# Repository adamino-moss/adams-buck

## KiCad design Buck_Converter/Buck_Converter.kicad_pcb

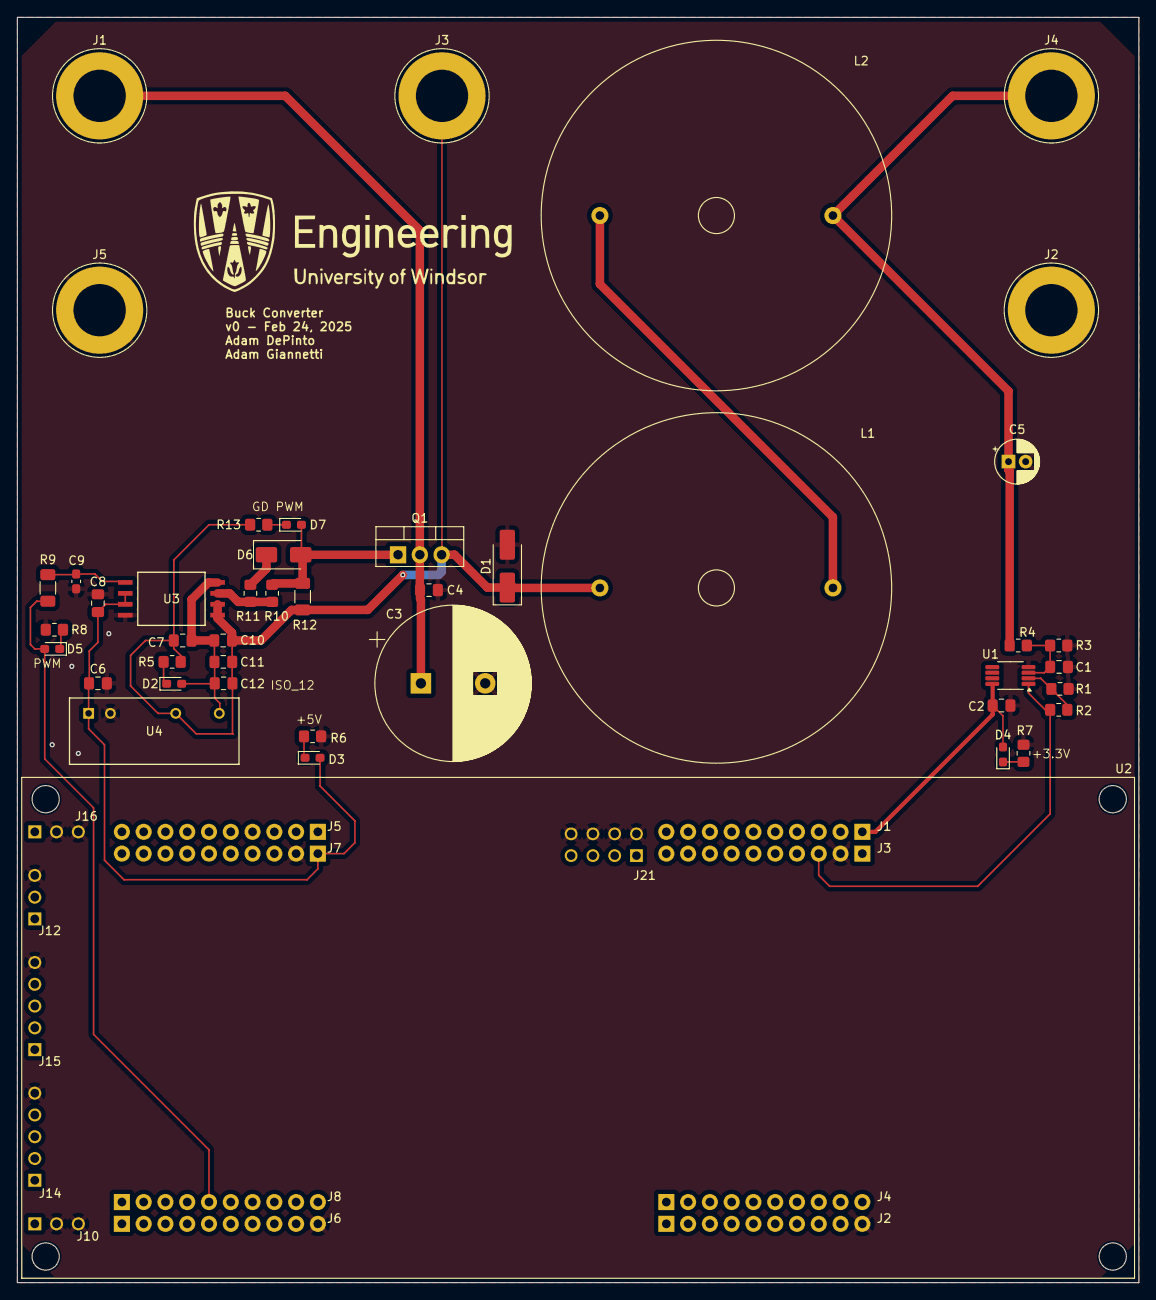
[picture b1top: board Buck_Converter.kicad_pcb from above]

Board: 2 copper layers, 130.8 x 147.6 mm, 44 parts (0 on the bottom side), 21 nets.

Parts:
C1: 1.2u; C_0805_2012Metric_Pad1.18x1.45mm_HandSolder
C2, C4, C6, C7, C8: 1u; C_0805_2012Metric_Pad1.18x1.45mm_HandSolder
C3: 470u; CP_Radial_D18.0mm_P7.50mm
C5: 3.3u; CP_Radial_D5.0mm_P2.00mm
C9: 33pF; C_0603_1608Metric_Pad1.08x0.95mm_HandSolder
C10, C12: 10u; C_0805_2012Metric_Pad1.18x1.45mm_HandSolder
C11: 220n; C_0805_2012Metric_Pad1.18x1.45mm_HandSolder
D1: SS310; D_SMA_Handsoldering
D2, D3, D4, D5, D7: LTST-C190GKT; LED_0603_1608Metric_Pad1.05x0.95mm_HandSolder
D6: US2AA; D_SMA
J1, J2, J3, J4, J5: Conn_01x01_Pin; Banana_Jack_1Pin
L1, L2: 12m; L_Radial_D40.6mm_P27.18mm_Vishay_IHB-4
Q1: IRF540N; TO-220-3_Vertical
R1, R4: 40k; R_0805_2012Metric_Pad1.20x1.40mm_HandSolder
R2, R3: 2k; R_0805_2012Metric_Pad1.20x1.40mm_HandSolder
R5, R13: 1k; R_0805_2012Metric_Pad1.20x1.40mm_HandSolder
R6: 300; R_0805_2012Metric_Pad1.20x1.40mm_HandSolder
R7, R8: 120; R_0805_2012Metric_Pad1.20x1.40mm_HandSolder
R9: 51; R_1206_3216Metric_Pad1.30x1.75mm_HandSolder
R10: 7.5; R_0805_2012Metric_Pad1.20x1.40mm_HandSolder
R11: 12; R_0805_2012Metric_Pad1.20x1.40mm_HandSolder
R12: 50; R_1206_3216Metric_Pad1.30x1.75mm_HandSolder
U1: LM358; VSSOP-8_3x3mm_P0.65mm
U2: LAUNCHXL-F28379D; MOD_LAUNCHXL-F28379D
U3: UCC5304DWVR; SOIC8_DWV_TEX
U4: TMV 0512SHI; TMV-HI_SINGLE_TRP

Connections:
+3.3V: C2.1, D4.2 (A), U1.8 (V+), U2.J1_1 (3.3V_J1)
+5V: C6.1, C8.1, D3.2 (A), U2.J7_1 (+5V_J7), U3.2 (VCCI), U3.3 (VCCI), U4.1 (+VIN(VCC))
/GD/GD_PWM: R10.1, R11.1, U3.7 (OUT)
/GD/ISO_12: C7.1, C10.1, C11.1, C12.1, D2.2 (A), U3.8 (VDD), U4.7 (+VOUT)
/GD/PWM_FILT: C9.1, R9.2, U3.1 (IN)
/PWM: D5.2 (A), R9.1, U2.J8_5 (GPIO11/PWMOUT6B)
/PowerStage/VIN: C3.1, C4.1, J1.1, Q1.2 (D)
/VFILT: R2.2, U1.1, U2.J3_3 (ADCIN14/ANALOGIN)
/VG: D6.2 (A), D7.2 (A), Q1.1 (G), R10.2, R12.2
/VOUT: C5.1, J4.1, L2.2, R4.2
/VSW: C7.2, C10.2, C11.2, C12.2, D1.1 (K), J3.1, L1.1, Q1.3 (S), R5.2, R12.1, R13.2, U3.5 (VSS), U3.6 (VSS), U4.5 (-VOUT)
GND: C1.2, C2.2, C3.2, C4.2, C5.2, C6.2, C8.2, C9.2, D1.2 (A), J2.1, J5.1, R1.1, R3.1, R6.2, R7.2, R8.2, U1.4 (V-), U2.J2_10 (GND_J2), U2.J3_2 (GND_J3), U2.J6_10 (GND_J6), U2.J7_2 (GND_J7), U2.J10_2 (GND_J10), U2.J10_3 (GND_J10__1), U2.J12_3 (GND_J12), U2.J14_5 (GND_J14), U2.J15_5 (GND_J15), U2.J16_2 (GND_J16), U2.J16_3 (GND_J16__1), U2.J21_2 (TP21/GND), U2.J21_4 (TP22/GND), U2.J21_6 (TP23/GND), U2.J21_8 (TP24/GND), U3.4 (GND), U4.2 (-VIN(GGND))
unnamed: D2.1 (K), R5.1
unnamed: D3.1 (K), R6.1
unnamed: D4.1 (K), R7.1
unnamed: D5.1 (K), R8.1
unnamed: D6.1 (K), R11.2
unnamed: D7.1 (K), R13.1
unnamed: L1.2, L2.1
unnamed: C1.1, R3.2, R4.1, U1.3 (+)
unnamed: R1.2, R2.1, U1.2 (-)

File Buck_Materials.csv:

Reference,Value,Qty,DNP,#,Part Number
D6,US2AA,1,,1,US2AA
U3,UCC5304DWVR,1,,2,UCC5304DWVR
U4,TMV 0512SHI,1,,3,TMV 0512SHI
"C2,C6,C7,C8",1u,4,,4,TAJR105K025RNJ
D1,SS310,1,,5,SS310
"R5,R13",1k,2,,6,RNCP0805FTD1K00
R6,300,1,,7,RMCF0805JT300R
"R7,R8",120,2,,8,RMCF0805FT120R
R12,50,1,,9,RCP1206W50R0JTP
R9,51,1,,10,RC1206FR-0751RL
R11,12,1,,11,RC0805FR-0712RL
"R2,R3",2k,2,,12,RC0805FR-072KL
"D2,D3,D4,D5,D7",LTST-C190GKT,5,,13,LTST-C190GKT
U1,LM358,1,,14,LM358DGKR
U2,LAUNCHXL-F28379D,1,,15,LAUNCHXL-F28379D
Q1,IRF540N,1,,16,IRF540NPBF
C12,10u,1,,17,GRM21BR61E106KA73L
C4,1u,1,,18,GRM21BC72A105KE01L
C10,10u,1,,19,F951C106MPAAQ2
R10,7.5,1,,20,CRCW08057R50FKEAHP
"R1,R4",40k,2,,21,CRCW080540K0FKEA
C11,220n,1,,22,C0805C224K5RACTU
C1,1.2u,1,,23,C0805C125K4PACTU
C9,33pF,1,,24,C0603C330J5GACTU
"J1,J2,J3,J4,J5",Conn_01x01_Pin,5,,25,BU-P72930-2
"L1,L2",12m,2,,26,1140-123K-RC
C3,470u,1,,27,100ZLH470MEFC16X31.5
C5,3.3u,1,,28,860020772007
Heat Sink,,1,,29,577202B00000G
Mounting Kit,,1,,30,4880G
MUC Conn,,4,,31,TSW-110-07-F-D

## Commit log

2025-02-25 Add files via upload
    Main KiCAD filts
2025-02-25 Add files via upload
    3D model for banana connectors
2025-02-25 Add files via upload
    3D model and symbol for the LAUNCHPAD MCU
2025-02-25 Add files via upload
    3D model and symbol for the power supply
2025-02-25 Add files via upload
    3D model and symbol for the gate driver
2025-02-25 Add files via upload
    Footprint for the University logo
2025-02-25 Add files via upload
    Added the BOM
2025-03-03 Add files via upload
    Revised Buck Converter schematic and PCB, BOM, and gerber files
